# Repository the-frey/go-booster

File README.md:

# Go! Booster pedal

Project files for the Go! Booster. Note that the template in the board file is for the standard drilling that I use - you can ignore it, as it's not a visible layer for the sake of board export or manufacturing setup.

Hopefully at some point I will remember to upload an offboard wiring mini PCB for the 3PDT switch you will need.

The 3mm LED in the opamp feedback path will add some clipping; a heavy clipping diode like a germanium diode might cause too much signal loss, so if you're going to experiment, then socket the diode.

I personally tend to leave it blank; the production Go! doesn't have anything in that spot.

Finally, obviously you can wire the treble control up to an actual pot. This PCB should just about fit in a 1590A, but I choose to put it in a roomier 125B as I prefer the form factor.

Happy hacking!

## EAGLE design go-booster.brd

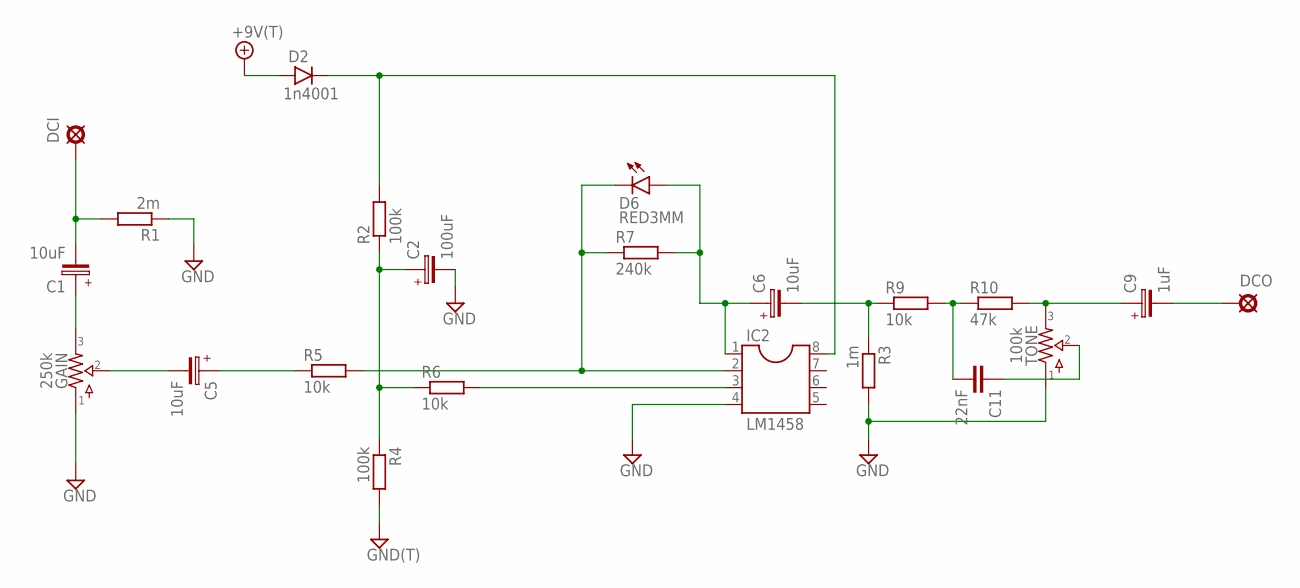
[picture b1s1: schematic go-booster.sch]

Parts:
+9V2: +9V(T); SQUARE
C1, C5, C6: 10uF; 050_020_1
C2: 100uF; 050_020_1
C9: 1uF; 050_020_1
C11: 22nF; 072X025
D2: 1n4001; DO41-4
D6: RED3MM; LED3MM
DCI: IN; OCTOGON
DCO: OUT; OCTOGON
GAIN: 250k; 16MM_CENTERMOUNT
GND11: GND(T); SQUARE
IC2: LM1458; SOCKET-08
R1: 2m; 0207/10
R2, R4: 100k; 0207/10
R3: 1m; 0207/10
R5, R6, R9: 10k; 0207/10
R7: 240k; 0207/10
R10: 47k; 0207/10
TONE: 100k; 2262_TRIM

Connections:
+9V: +9V2.1, D2.A
GND: C2.-, GAIN.1, GND11.1, IC2.4, R1.1, R3.2, R4.2, TONE.1
unnamed: C1.+, GAIN.3
unnamed: C1.-, DCI.1, R1.2
unnamed: D2.C, IC2.8, R2.2
unnamed: D6.K (C), IC2.2, R5.2, R7.1
unnamed: IC2.3, R6.2
unnamed: C6.+, D6.A, IC2.1, R7.2
unnamed: C5.-, GAIN.2
unnamed: C2.+, R2.1, R4.1, R6.1
unnamed: C6.-, R3.1, R9.1
unnamed: C5.+, R5.1
unnamed: C9.-, DCO.1
unnamed: C11.2, R9.2, R10.1
unnamed: C9.+, R10.2, TONE.3
unnamed: C11.1, TONE.2

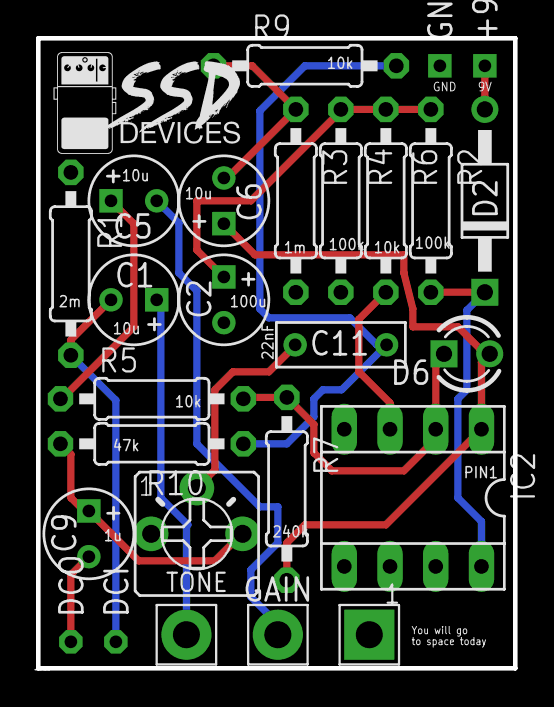
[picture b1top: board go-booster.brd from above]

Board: 2 copper layers, 26.5 x 35.0 mm, 24 parts (0 on the bottom side), 16 nets.

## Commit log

2017-09-05 Changed readme.
2017-09-05 Updated README, added project files.
